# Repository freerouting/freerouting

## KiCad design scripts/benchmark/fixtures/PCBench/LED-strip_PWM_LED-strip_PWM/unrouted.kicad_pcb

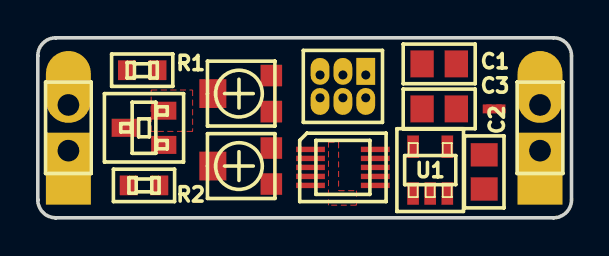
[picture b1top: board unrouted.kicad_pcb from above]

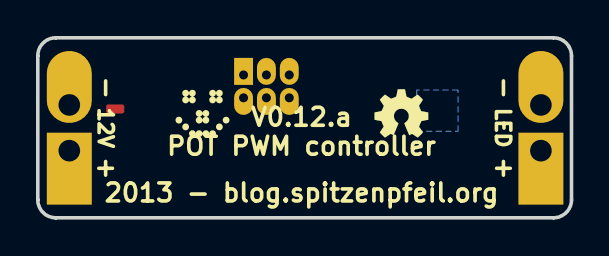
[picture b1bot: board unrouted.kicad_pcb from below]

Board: 2 copper layers, 29.7 x 10.0 mm, 16 parts (2 on the bottom side), 12 nets, no tracks yet.

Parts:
C1, C2: 100nF; MADW__C0805
C3: 4.7µF; MADW__C0805
G1: OSHW-logo_silkscreen_3mm
G2: LED_smile_silkscreen_3mm
IC1: MADW__ATTINY13-MM; MADW__MLF10
JP1: ISP; MADW__PIN_ARRAY_3x2_1.27mm
NJ1: NET-JOIN; MADW__SMD-net-noin-0.5mm
P1, P2: CONN_2; MADW__SIL-2
R1: 100k; MADW__R0603_2
R2: 150R; MADW__R0603_2
RV1, RV2: 50k; MADW__TC33X-POT
T1: AO3400; MADW__SOT23
U1: MCP1804-SOT23-5; MADW__SOT23-5

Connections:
/MISO: IC1.7, JP1.1
/MOSI: IC1.6, JP1.4, R1.2, R2.1
/POT1: IC1.2, RV1.2
/POT2: IC1.4, RV2.2
/RESET: IC1.1, JP1.5
/SCK: IC1.9, JP1.3
/Vin: C2.1, P1.1, P2.1, U1.1, U1.4
/drain: P2.2, T1.3
GND: C1.2, C3.2, IC1.5, JP1.6, NJ1.1, RV1.3, RV2.1
GNDPWR: C2.2, NJ1.2, P1.2, R1.1, T1.2, U1.2
unnamed: R2.2, T1.1
VCC: C1.1, C3.1, IC1.10, JP1.2, RV1.1, RV2.3, U1.5

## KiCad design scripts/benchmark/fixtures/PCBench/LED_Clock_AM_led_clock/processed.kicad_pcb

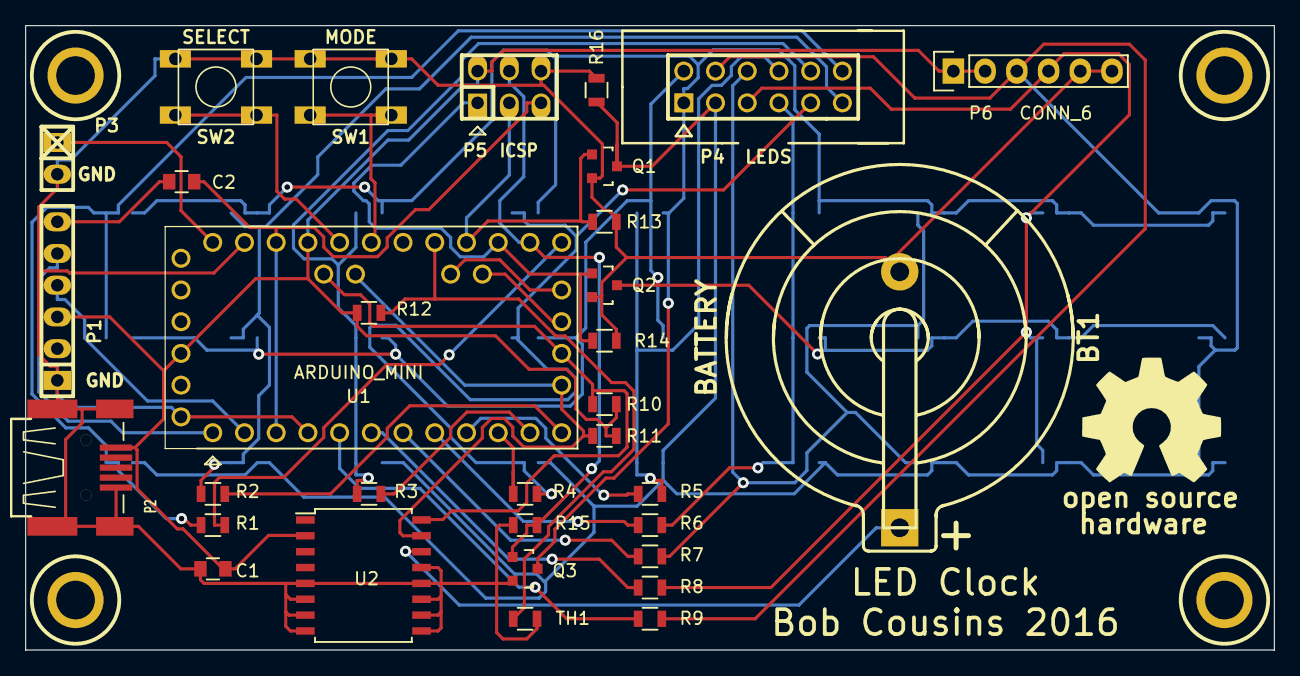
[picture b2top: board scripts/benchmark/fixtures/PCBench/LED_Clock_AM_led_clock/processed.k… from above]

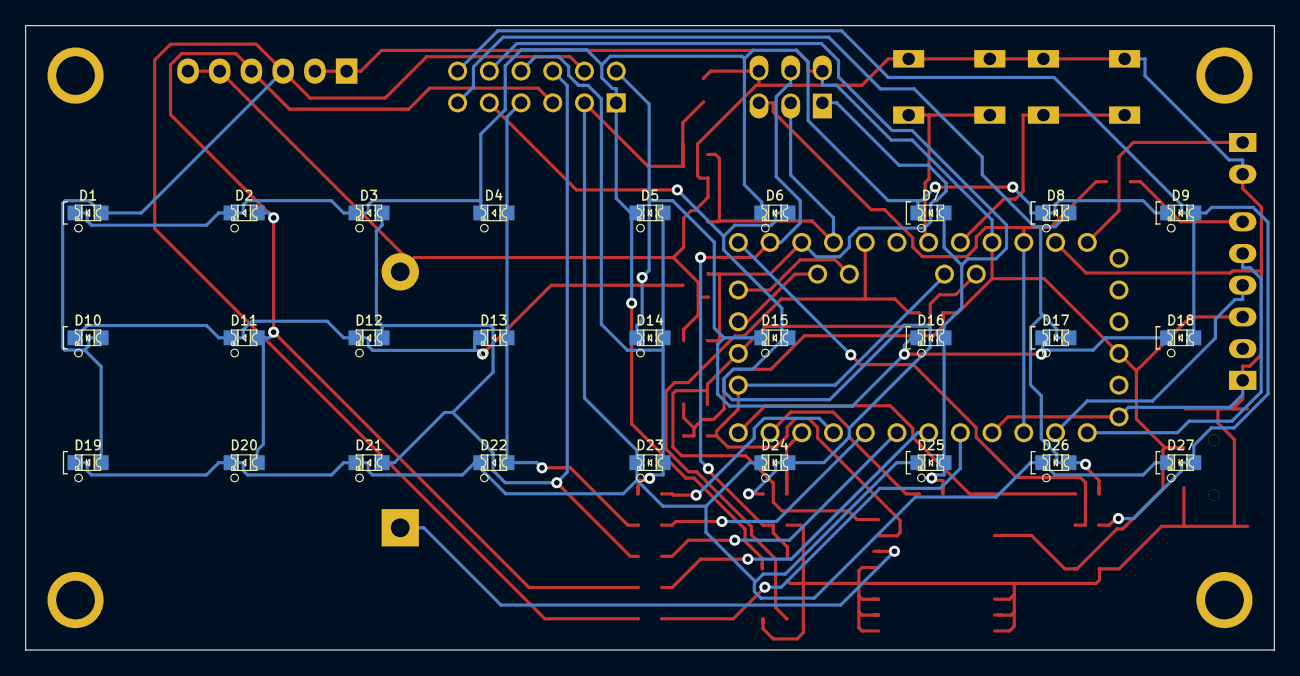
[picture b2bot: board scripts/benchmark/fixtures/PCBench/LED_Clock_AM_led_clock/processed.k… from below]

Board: 2 copper layers, 100.0 x 50.0 mm, 65 parts (27 on the bottom side), 37 nets.

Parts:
BT1: BATTERY; keystone_106
C1, C2: 100nF; C_0805
D1, D7, D8, D9, D10, D16, D17, D18, D19, D25, D26, D27: LED; LED-0805_RED
D2, D3, D4, D11, D12, D13, D20, D21, D22: LED; LED-0805_GREEN
D5, D6, D14, D15, D23, D24: LED; LED-0805_BLUE
H1, H2, H3, H4: HOLE_RMC; HOLE_M3
M2: LOGO_OSHW; OSHW_logo_2
P1: SERIAL; pin_strip_6
P2: USBCONN; CONN_MiniAB_SMT_RMC
P3: 5-9V IN; pin_strip_2
P4: LEDS; PIN_ARRAY_6x2_RMC
P5: ICSP; pin_strip_3x2
P6: CONN_6; Pin_Header_Straight_1x06
Q1, Q2, Q3: BSS138; SOT-23
R1, R2, R3, R4, R5, R6, R7, R8, R9: 220; R_0805
R10, R11, R12: 4k7; R_0805
R13, R14, R15: 10k; R_0805
R16: 0R; R_0805
SW1: MODE; SW_6x6_MULTI
SW2: SELECT; SW_6x6_MULTI
TH1: 10k; R_0805
U1: ARDUINO_MINI
U2: DS3231N; SOIC-16_7.5x10.3mm_Pitch1.27mm

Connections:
+5V: C1.1, P1.3, P2.1, P5.2, P6.1, P6.2, R10.2, R11.2, R12.1, U1.+5V, U2.2
/MISO: P5.1, Q2.1, R14.1, U1.12
/MOSI: P5.4, Q3.1, R15.1, U1.11
/SCK: P5.3, Q1.1, R13.1, U1.13
/SCL: R10.1, U1.A5, U2.16
/SDA: R11.1, U1.A4, U2.15
/SW1: SW1.1, U1.A2
/SW2: SW2.1, U1.A3
/VIN: P3.1, U1.VIN
/~RST: C2.2, P5.5, U1.RST
COL1: D1.2, D10.2, D19.2, P4.4, P6.3, R9.2
COL2: D2.2, D11.2, D20.2, P4.5, P6.4, R8.2
COL3: D3.2, D12.2, D21.2, P4.6, R7.2
COL4: D4.2, D13.2, D22.2, P4.7, R6.2
COL5: D5.2, D14.2, D23.2, P4.8, R5.2
COL6: D6.2, D15.2, D24.2, P4.9, R4.2
COL7: D7.2, D16.2, D25.2, P4.10, R3.2
COL8: D8.2, D17.2, D26.2, P4.11, R2.2
COL9: D9.2, D18.2, D27.2, P4.12, R1.2
GND: BT1.2, C1.2, P1.1, P2.4, P2.5, P3.2, P5.6, P6.5, P6.6, Q1.2, Q2.2, Q3.2, R13.2, R14.2, R15.2, R16.2, SW1.2, SW2.2, TH1.2, U1.GND, U2.5, U2.6, U2.7, U2.8, U2.9, U2.10, U2.11, U2.12, U2.13
unnamed: BT1.1, U2.14
unnamed: C2.1, P1.6
unnamed: R1.1, U1.10
unnamed: R2.1, U1.9
unnamed: R3.1, U1.8
unnamed: R4.1, U1.7
unnamed: R5.1, U1.6
unnamed: R6.1, U1.5
unnamed: R7.1, U1.4
unnamed: R8.1, U1.3
unnamed: R9.1, U1.2
unnamed: R12.2, TH1.1, U1.A0
ROW1: D1.1, D2.1, D3.1, D4.1, D5.1, D6.1, D7.1, D8.1, D9.1, P4.1, Q3.3
ROW2: D10.1, D11.1, D12.1, D13.1, D14.1, D15.1, D16.1, D17.1, D18.1, P4.2, Q2.3
ROW3: D19.1, D20.1, D21.1, D22.1, D23.1, D24.1, D25.1, D26.1, D27.1, P4.3, Q1.3, R16.1
RX: P1.4, U1.0
TX: P1.5, U1.1

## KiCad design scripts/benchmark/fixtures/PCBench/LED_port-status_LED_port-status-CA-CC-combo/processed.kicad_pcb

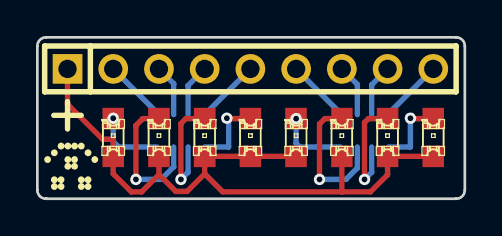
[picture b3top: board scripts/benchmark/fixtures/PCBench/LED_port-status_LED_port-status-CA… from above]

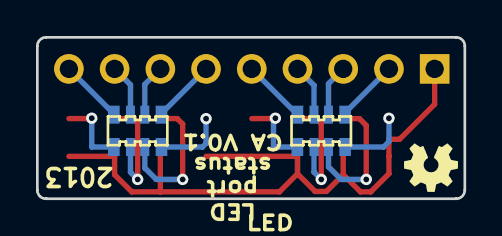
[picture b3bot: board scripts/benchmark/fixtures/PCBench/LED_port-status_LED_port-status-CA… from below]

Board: 2 copper layers, 23.7 x 9.0 mm, 15 parts (4 on the bottom side), 17 nets.

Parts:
D1, D2, D3, D4, D5, D6, D7, D8: LED; LED-0805
G1, G1_2: LED_smile_silkscreen_3mm
G2, G2_2: OSHW-logo_silkscreen_3mm
P1: CONN_9; SIL-9
RP1, RP2: 1k; MADW__1206*4_resistor_array

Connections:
unnamed: P1.9, RP1.4
unnamed: P1.8, RP1.3
unnamed: P1.7, RP1.2
unnamed: P1.6, RP1.1
unnamed: P1.5, RP2.4
unnamed: P1.4, RP2.3
unnamed: P1.3, RP2.2
unnamed: P1.2, RP2.1
unnamed: D1.2, RP1.5
unnamed: D6.2, RP2.6
unnamed: D8.2, RP2.8
unnamed: D5.2, RP2.5
unnamed: D4.2, RP1.8
unnamed: D2.2, RP1.6
unnamed: D7.2, RP2.7
unnamed: D3.2, RP1.7
unnamed: D1.1, D2.1, D3.1, D4.1, D5.1, D6.1, D7.1, D8.1, P1.1
